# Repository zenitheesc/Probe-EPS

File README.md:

<h1 align="center" style="color:white; background-color:black">Probe-EPS</h1>
<h4 align="center">Eletrical power system for stratospheric probes, using Zenith Stack</h4>

<p align="center">

</p>

<p align="center">
    <a href="#environment-and-tools">Environment and Tools</a> •
    <a href="#z-hub">Z-Hub</a> •
    <a href="#aroca-(battery)-eps">Aroca (Battery) EPS</a> •
    <a href="#london-(power)-eps">London (Power) EPS</a>
</p>

This configuration of the Eletrical power system requires a board that monitors the charger and battery, in addition to performing thermal control.

## Environment and tools

This system was designed using Eagle v.9.4.2

## Z-Hub

<a href="https://github.com/zenitheesc/Probe-EPS/tree/main/Hardware/Aroca_EPS-v.2.0"><h2>Aroca (Battery) EPS</h2></a>

This subsystem is primarily responsible for the active thermal control of the batteries, in addition to supporting battery monitoring and load balancing

<a href="https://github.com/zenitheesc/Probe-EPS/tree/main/Hardware/London_EPS-v.2.0"><h2>London (Power) EPS</h2></a>

Functioning as an extension of the previous subsystem, it performs conversions of battery voltage levels to the levels requested within the hardware, making the necessary distribution, as well as controlling the loading of batteries through solar panels.

---

<p align="center">

</p>
<p align = "center">
<a href="zenith.eesc@gmail.com">zenith.eesc@gmail.com</a>
</p>

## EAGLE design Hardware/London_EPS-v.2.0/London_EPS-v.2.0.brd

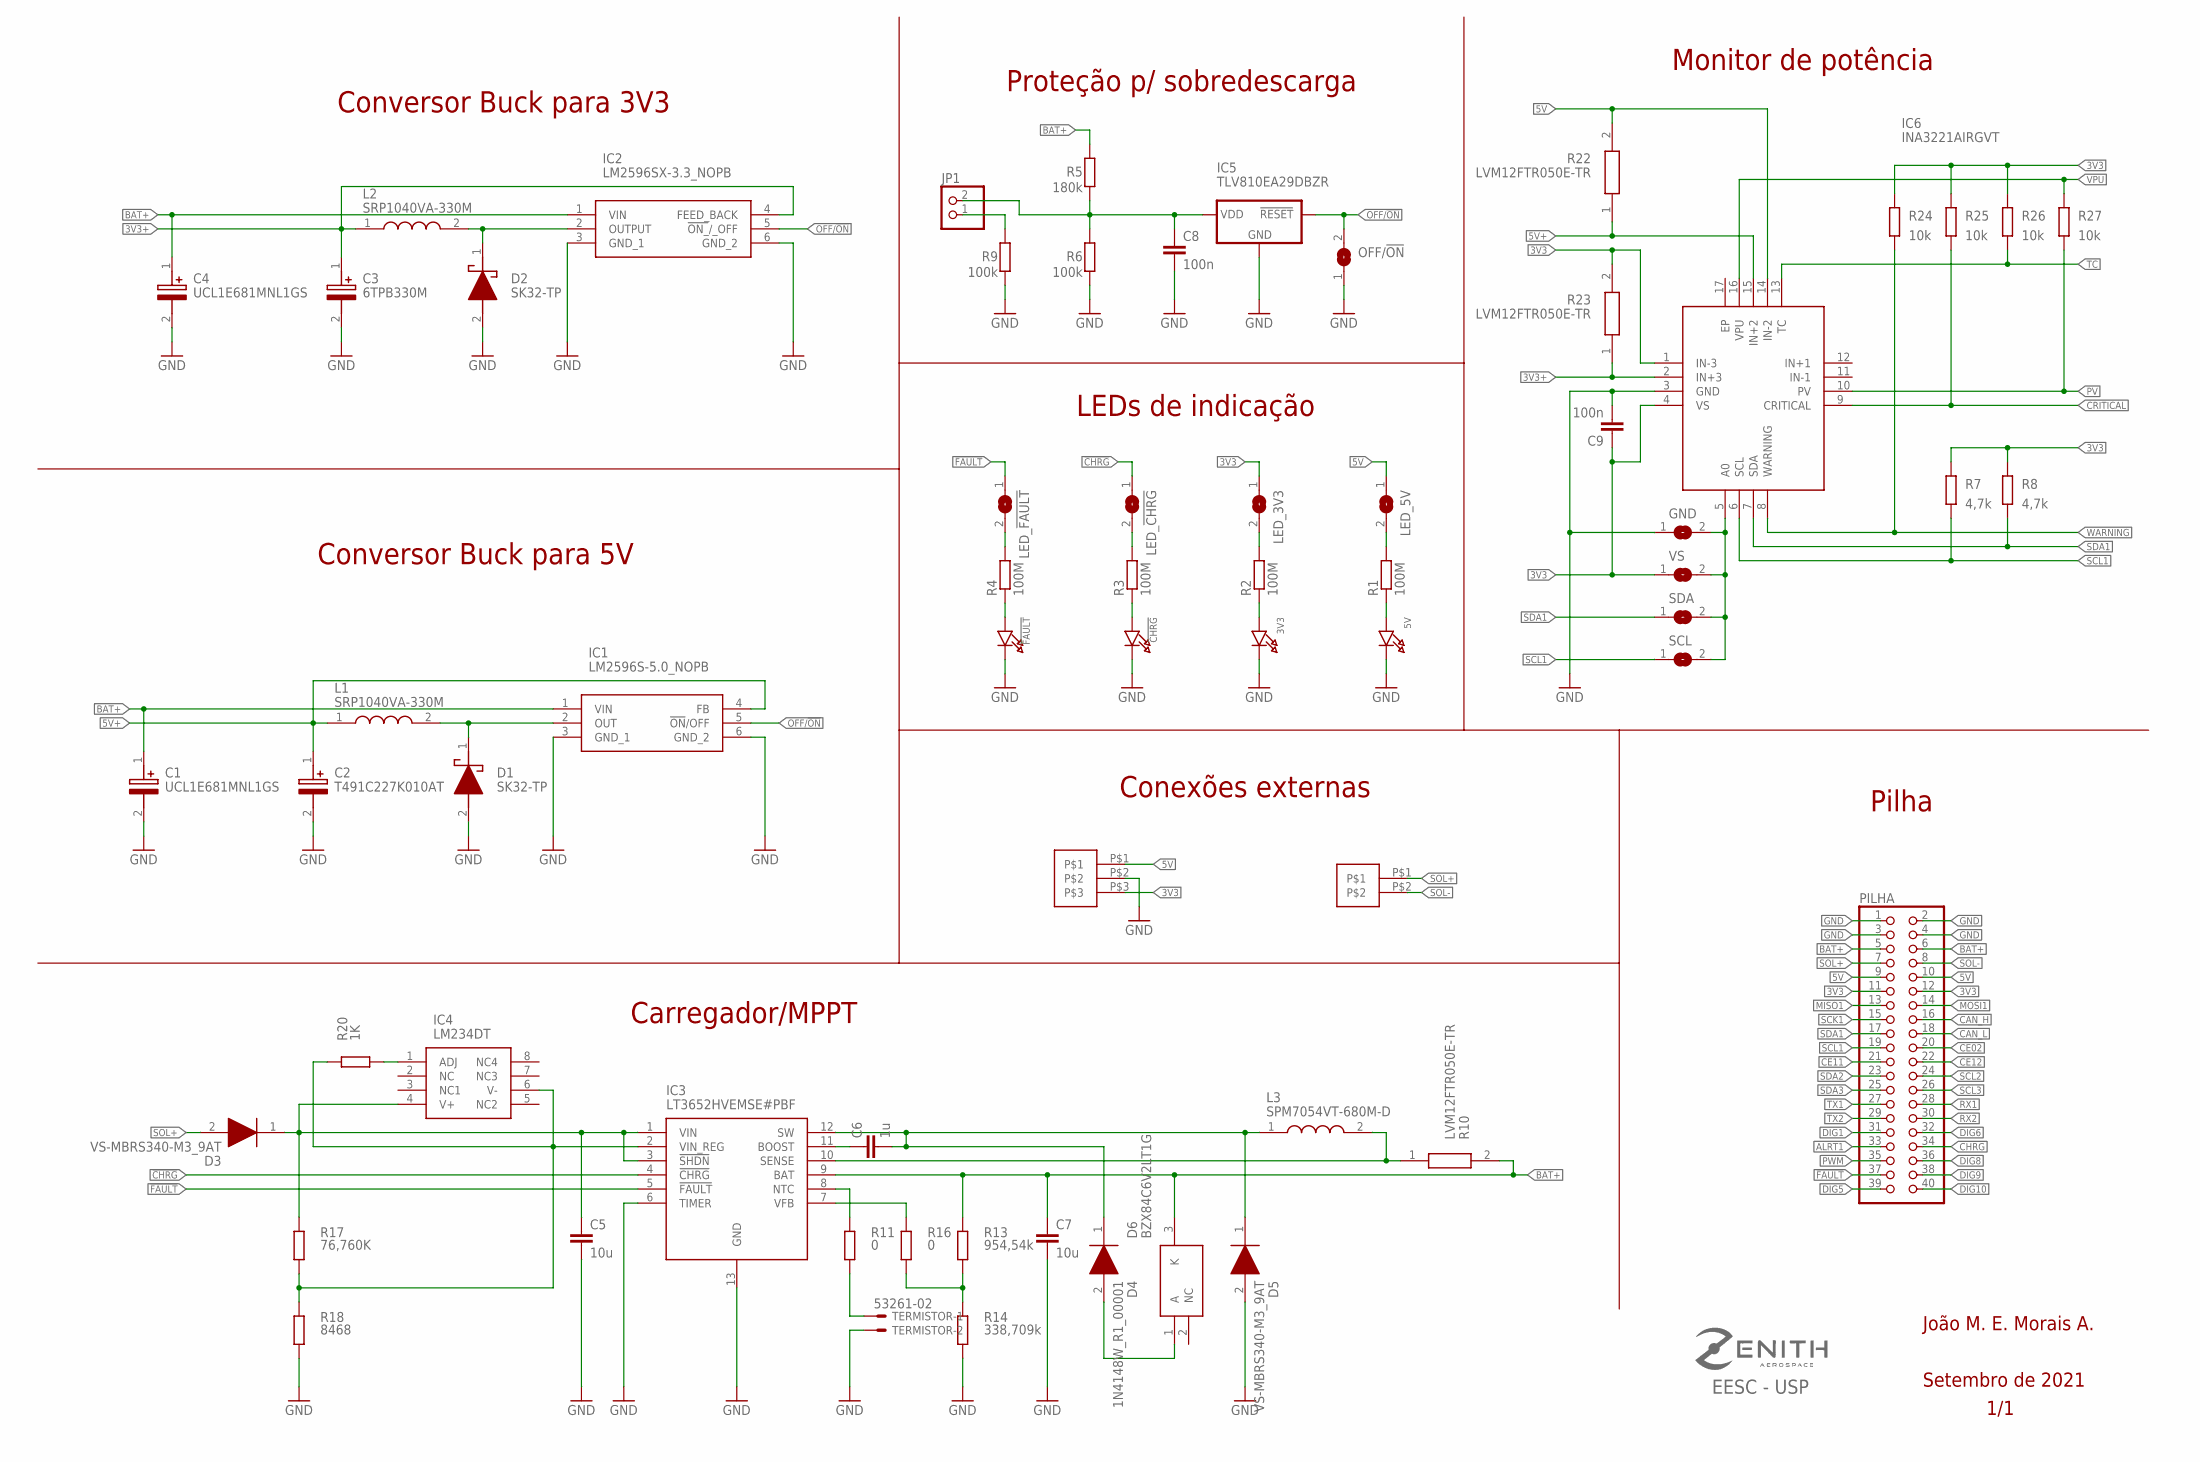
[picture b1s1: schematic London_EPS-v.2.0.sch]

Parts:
3V3, 5V: LED1206; CHIPLED_1206
!CHRG: LED1206; CHIPLED_1206
!FAULT: LED1206; CHIPLED_1206
C1, C4: UCL1E681MNL1GS; CAPAE1030X1400N
C2: T491C227K010AT; CAPPM6032X280N
C3: 6TPB330M; 10TPF150ML
C5, C7: 10u; C0805
C6: 1u; C0805
C8, C9: 100n; C0805
D1, D2: SK32-TP; DIOM7959X262N@1
D3, D5: VS-MBRS340-M3_9AT; DIOM7959X262N
D4: 1N4148W_R1_00001; SOD3816X135N
D6: BZX84C6V2LT1G; SOT96P237X111-3N
GND: SOLDERJUMPERREFLOW_NOPASTE; SOLDERJUMPER_REFLOW_NOPASTE
IC1: LM2596S-5.0_NOPB; KTT0005B
IC2: LM2596SX-3.3_NOPB; KTT0005B
IC3: LT3652HVEMSE#PBF; SOP65P490X110-13N
IC4: LM234DT; SOIC127P600X175-8N
IC5: TLV810EA29DBZR; SOT23
IC6: INA3221AIRGVT; QFN65P400X400X100-17N
JP1: PINHD-1X2/90; 1X02/90
L1, L2: SRP1040VA-330M; INDPM110100X400N
L3: SPM7054VT-680M-D; SPM7054VT
LED_3V3, LED_5V: SOLDERJUMPERREFLOW_NOPASTE; SOLDERJUMPER_REFLOW_NOPASTE
LED_!CHRG: SOLDERJUMPERREFLOW_NOPASTE; SOLDERJUMPER_REFLOW_NOPASTE
LED_!FAULT: SOLDERJUMPERREFLOW_NOPASTE; SOLDERJUMPER_REFLOW_NOPASTE
OFF/!ON: SOLDERJUMPERREFLOW_NOPASTE; SOLDERJUMPER_REFLOW_NOPASTE
PILHA: PINHD-2X20; 2X20
R1, R2, R3, R4: 100M; R0805
R5: 180k; R0805
R6, R9: 100k; R0805
R7, R8: 4,7k; R0805
R10, R22, R23: LVM12FTR050E-TR; RESC3016X70N
R11, R16: 0; R0805
R13: 954,54k; R0805
R14: 338,709k; R0805
R17: 76,760K; R0805
R18: 8468; R0805
R20: 1K; R0805
R24, R25, R26, R27: 10k; R0805
SCL: SOLDERJUMPERREFLOW_NOPASTE; SOLDERJUMPER_REFLOW_NOPASTE
SDA: SOLDERJUMPERREFLOW_NOPASTE; SOLDERJUMPER_REFLOW_NOPASTE
TERMISTOR: 53261-02
U$1: S02B-XASS-1
U$2: S03B-XASS-1
VS: SOLDERJUMPERREFLOW_NOPASTE; SOLDERJUMPER_REFLOW_NOPASTE

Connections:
3V3: C9.1, IC6.1 (IN-3), IC6.4 (VS), LED_3V3.1, PILHA.11, PILHA.12, R7.2, R8.2, R23.2, R24.2, R25.2, R26.2, U$2.P$3, VS.1
3V3+: C3.1 (+), IC2.4 (FEED_BACK), IC6.2 (IN+3), L2.1, R23.1
5V: IC6.14 (IN-2), LED_5V.1, PILHA.9, PILHA.10, R22.2, U$2.P$1
5V+: C2.1 (+), IC1.4 (FB), IC6.15 (IN+2), L1.1, R22.1
!CHRG: IC3.4 (!CHRG), LED_!CHRG.1, PILHA.34
!FAULT: IC3.5 (!FAULT), LED_!FAULT.1, PILHA.37
ALRT1: PILHA.33
BAT+: C1.1 (+), C4.1 (+), C7.1, D6.3 (K), IC1.1 (VIN), IC2.1 (VIN), IC3.9 (BAT), PILHA.5, PILHA.6, R5.1, R10.2, R13.1
CAN_H: PILHA.16
CAN_L: PILHA.18
CE02: PILHA.20
CE11: PILHA.21
CE12: PILHA.22
CRITICAL: IC6.9 (CRITICAL), R25.1
DIG1: PILHA.31
DIG5: PILHA.39
DIG6: PILHA.32
DIG8: PILHA.36
DIG9: PILHA.38
DIG10: PILHA.40
GND: 3V3.C, 5V.C, !CHRG.C, !FAULT.C, C1.2 (-), C2.2 (-), C3.2 (-), C4.2 (-), C5.2, C7.2, C8.2, C9.2, D1.2 (A), D2.2 (A), D5.2 (A), GND.1, IC1.3 (GND_1), IC1.6 (GND_2), IC2.3 (GND_1), IC2.6 (GND_2), IC3.6 (TIMER), IC3.13 (GND), IC5.2 (GND), IC6.3 (GND), OFF/!ON.1, PILHA.1, PILHA.2, PILHA.3, PILHA.4, R6.2, R9.2, R14.2, R18.2, TERMISTOR.2, U$2.P$2
MISO1: PILHA.13
MOSI1: PILHA.14
unnamed: 5V.A, R1.1
unnamed: LED_5V.2, R1.2
unnamed: 3V3.A, R2.1
unnamed: LED_3V3.2, R2.2
unnamed: !CHRG.A, R3.1
unnamed: D2.1 (K), IC2.2 (OUTPUT), L2.2
unnamed: LED_!CHRG.2, R3.2
unnamed: D1.1 (K), IC1.2 (OUT), L1.2
unnamed: !FAULT.A, R4.1
unnamed: LED_!FAULT.2, R4.2
unnamed: C8.1, IC5.3 (VDD), JP1.2, R5.2, R6.1
unnamed: GND.2, IC6.5 (A0), SCL.2, SDA.2, VS.2
unnamed: JP1.1, R9.1
unnamed: IC3.10 (SENSE), L3.2, R10.1
unnamed: IC3.8 (NTC), R11.1
unnamed: R11.2, TERMISTOR.1
unnamed: C6.2, D4.1 (K), D5.1 (K), IC3.12 (SW), L3.1
unnamed: IC3.7 (VFB), R16.1
unnamed: R13.2, R14.1, R16.2
unnamed: C6.1, IC3.11 (BOOST)
unnamed: C5.1, D3.1 (K), IC3.1 (VIN), IC3.3 (!SHDN), IC4.4 (V+), R17.1
unnamed: IC3.2 (VIN_REG), IC4.6 (V-), R17.2, R18.1, R20.1
unnamed: IC4.1 (ADJ), R20.2
unnamed: D4.2 (A), D6.1 (A)
OFF/!ON: IC1.5 (!ON!/OFF), IC2.5 (!ON_!/_OFF), IC5.1 (!RESET), OFF/!ON.2
PV: IC6.10 (PV), R27.1
PWM: PILHA.35
RX1: PILHA.28
RX2: PILHA.30
SCK1: PILHA.15
SCL1: IC6.6 (SCL), PILHA.19, R7.1, SCL.1
SCL2: PILHA.24
SCL3: PILHA.26
SDA1: IC6.7 (SDA), PILHA.17, R8.1, SDA.1
SDA2: PILHA.23
SDA3: PILHA.25
SOL+: D3.2 (A), PILHA.7, U$1.P$1
SOL-: PILHA.8, U$1.P$2
TC: IC6.13 (TC), R26.1
TX1: PILHA.27
TX2: PILHA.29
VPU: IC6.16 (VPU), R27.2
WARNING: IC6.8 (WARNING), R24.1

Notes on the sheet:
C:/Users/marcu/Desktop/Ensino Superior/Graduação - Eng Elétrica/Zenith/zenith-v2.bmp
EESC - USP
Setembro de 2021
1/1
João M. E. Morais A.
Pilha
Monitor de potência
Carregador/MPPT
Conversor Buck para 5V
Conversor Buck para 3V3
Proteção p/ sobredescarga
LEDs de indicação
Conexões externas

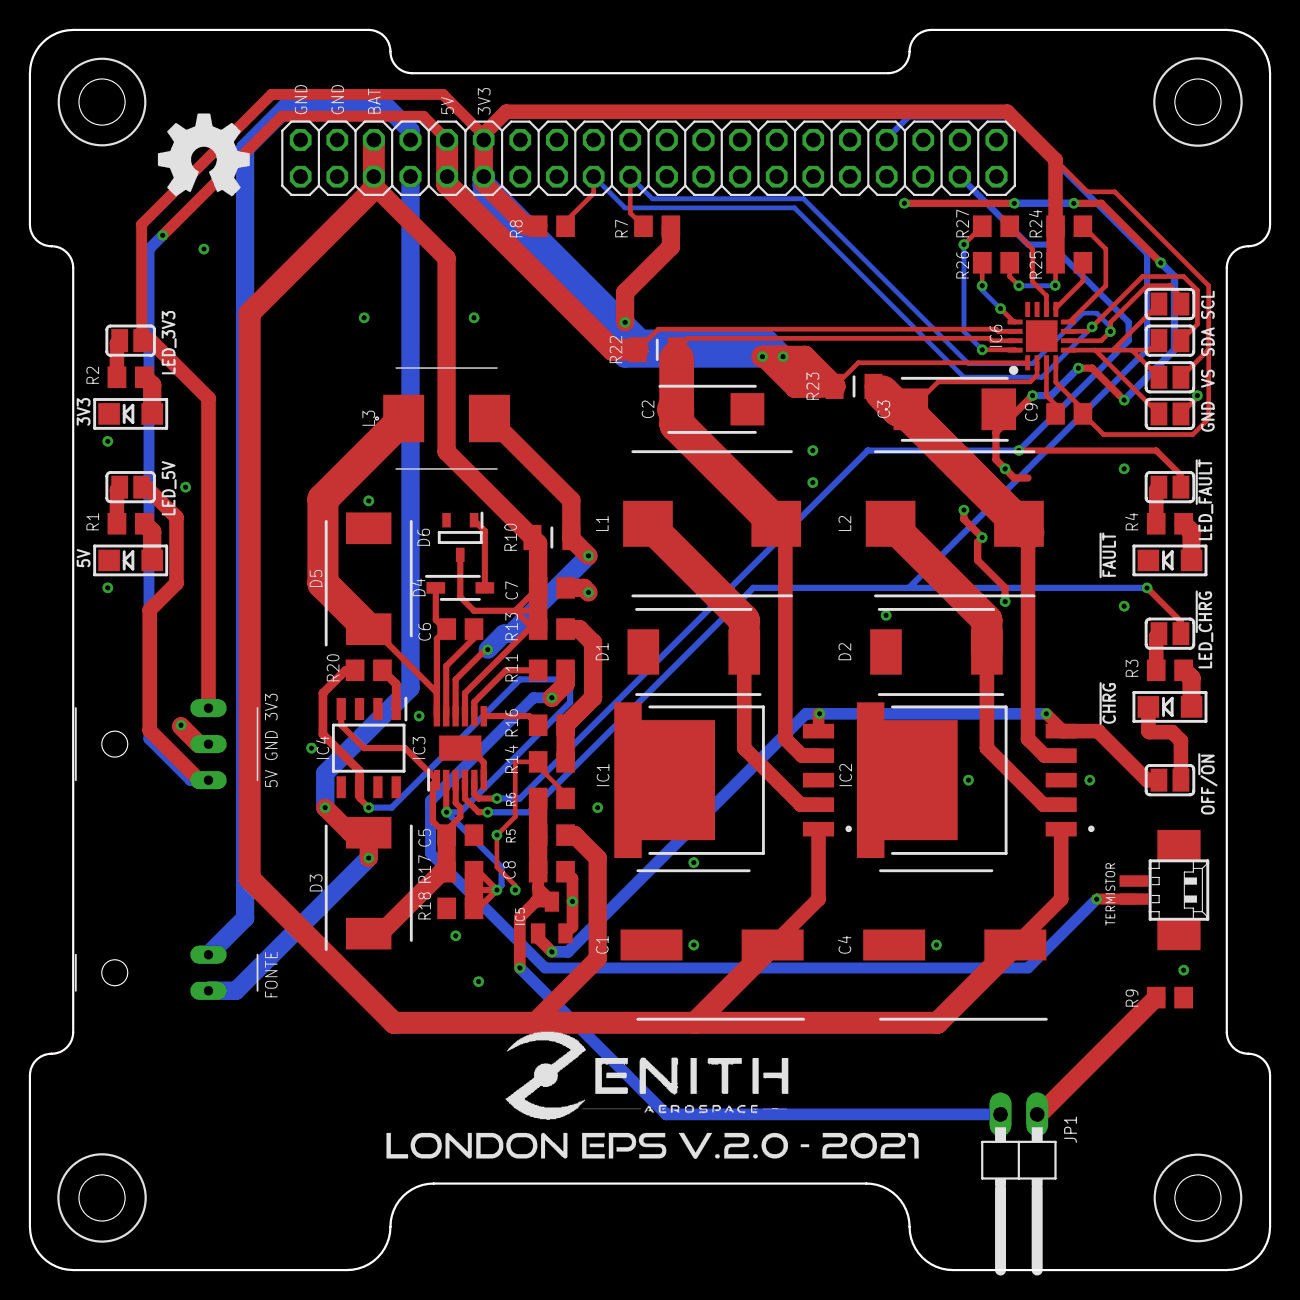
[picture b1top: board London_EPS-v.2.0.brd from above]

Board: 2 copper layers, 86.0 x 86.0 mm, 65 parts (0 on the bottom side), 42 nets.

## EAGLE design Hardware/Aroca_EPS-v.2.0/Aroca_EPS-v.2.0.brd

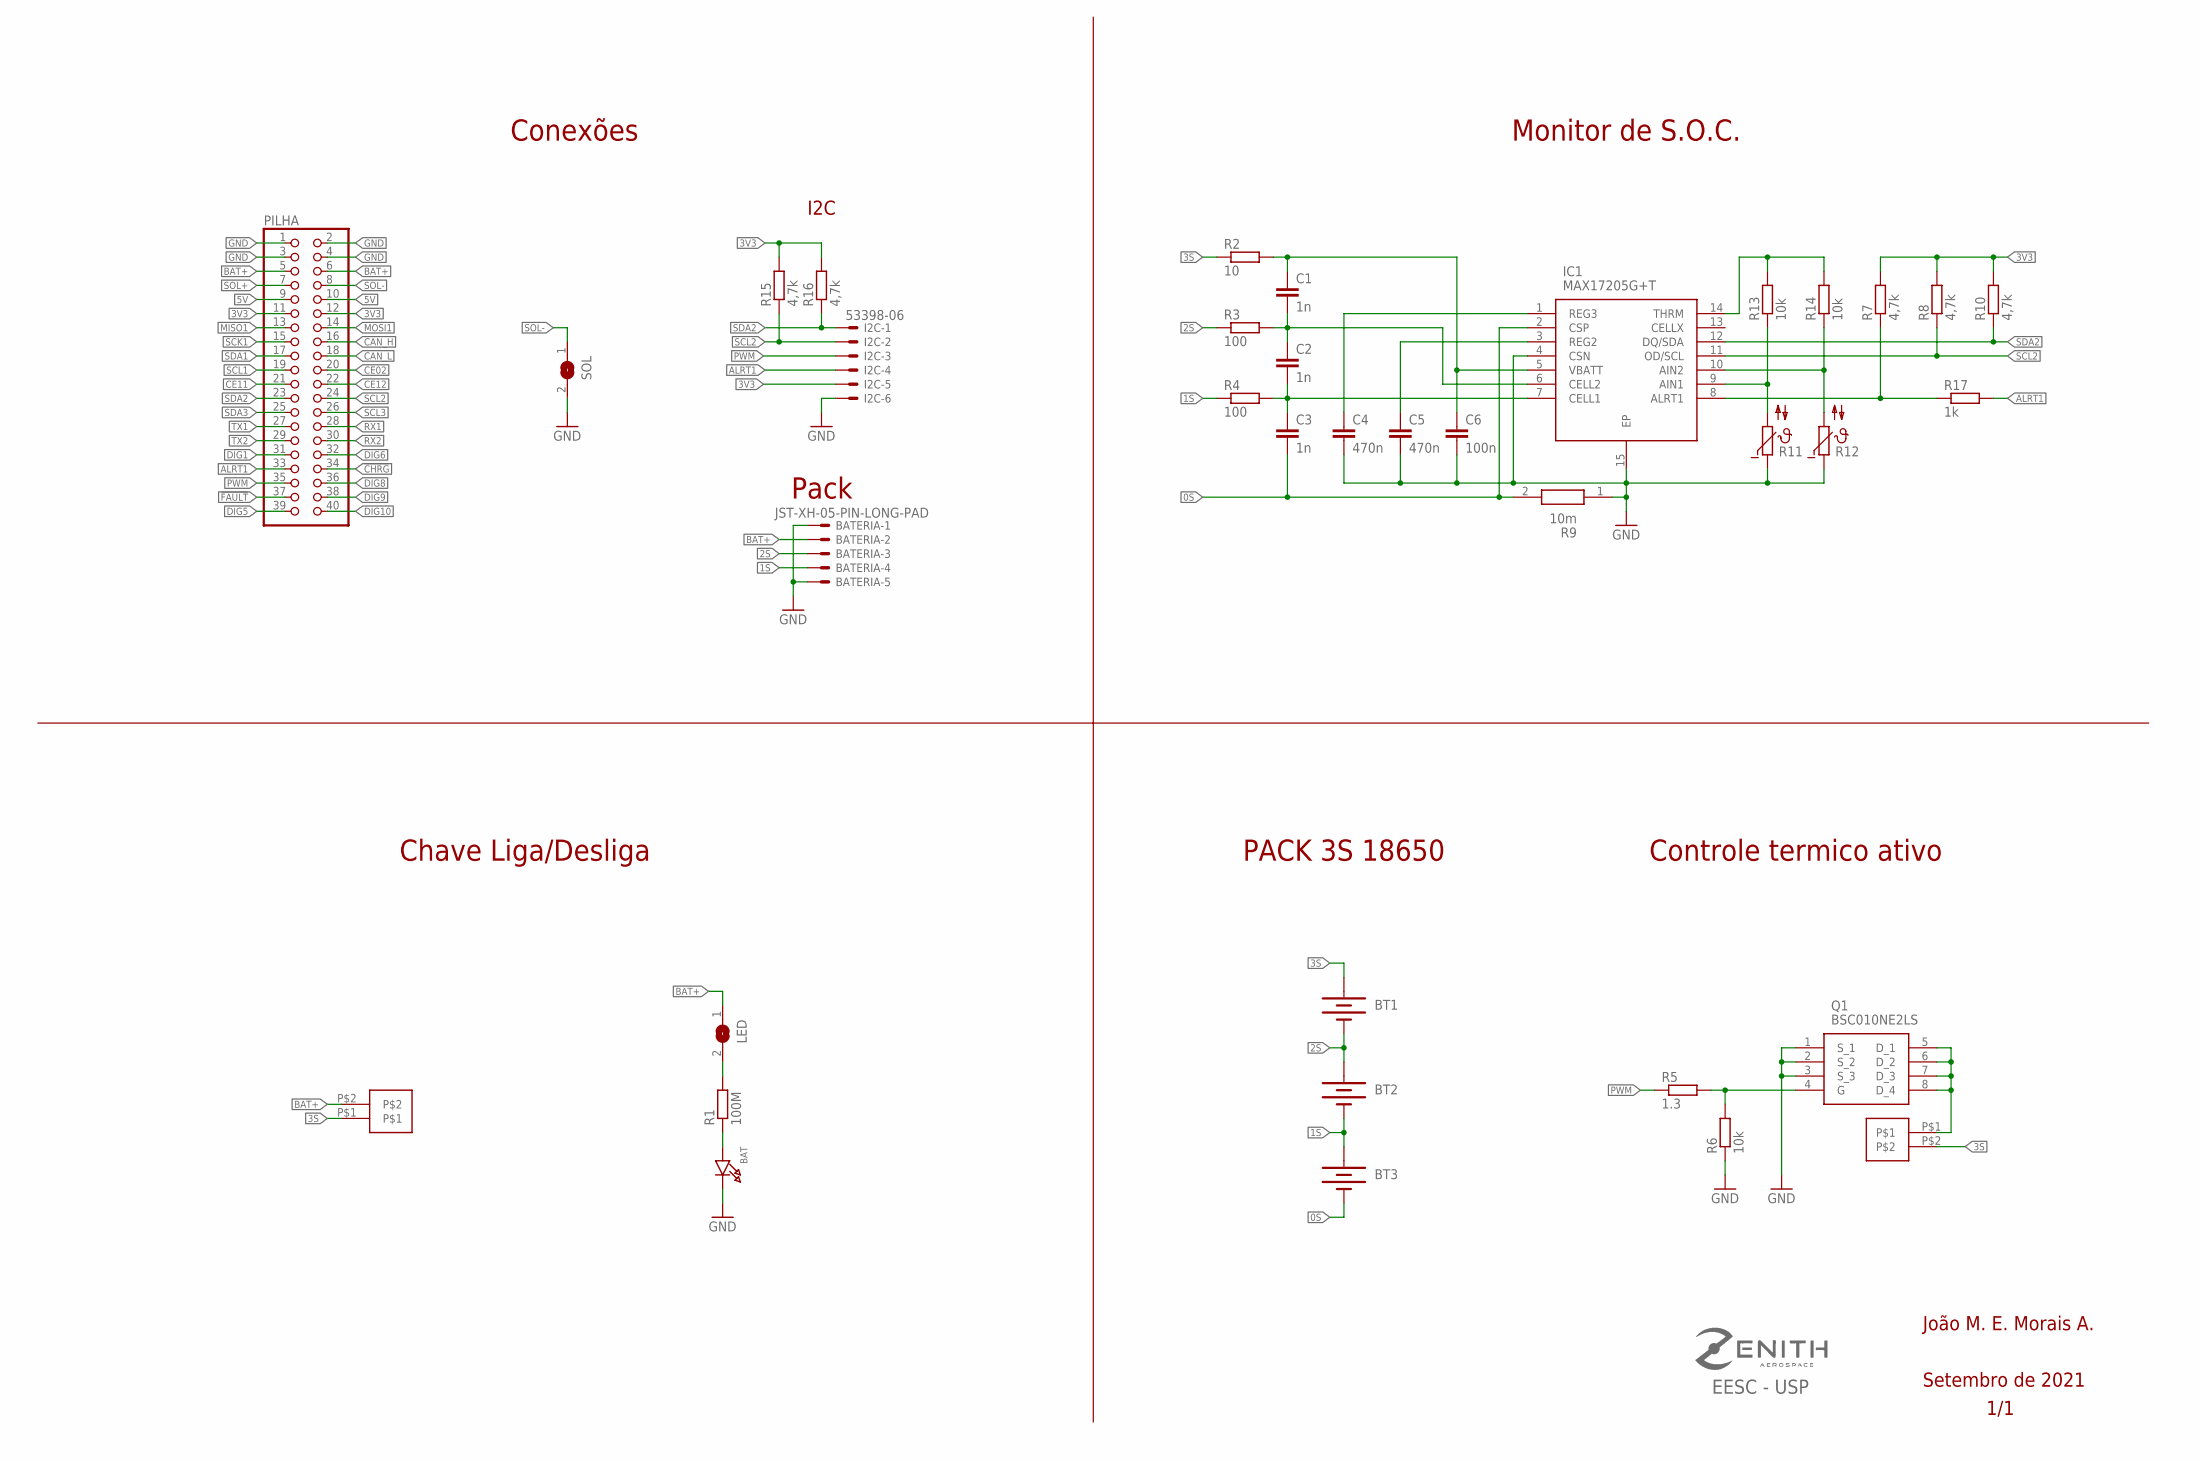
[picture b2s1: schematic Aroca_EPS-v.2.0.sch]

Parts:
BAT: LED1206; CHIPLED_1206
BATERIA: JST-XH-05-PIN-LONG-PAD; JST-XH-05-PACKAGE-LONG-PAD
BT1, BT2, BT3: BATTERY-18650; BATTERY_18650-HOLDER
C1, C2, C3: 1n; C0805
C4, C5: 470n; C0805
C6: 100n; C0805
I2C: 53398-06
IC1: MAX17205G+T; SON40P300X300X80-15N
LED: SOLDERJUMPERREFLOW_NOPASTE; SOLDERJUMPER_REFLOW_NOPASTE
PILHA: PINHD-2X20; 2X20
Q1: BSC010NE2LS; PG-TDSON-8
R1: 100M; R0805
R2: 10; 0204/7
R3, R4: 100; 0204/7
R5: 1.3; R0805
R6, R13, R14: 10k; R0805
R7, R8, R10, R15, R16: 4,7k; R0805
R9: 10m; GMR320HJBFA10L0
R11, R12: NTC640; P640
R17: 1k; R0805
SOL: SOLDERJUMPERREFLOW_NOPASTE; SOLDERJUMPER_REFLOW_NOPASTE
U$1: S02B-XASS-1
U$2: B02B-XASK-1

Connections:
0S: BT3.GND@1 (-), C3.2, IC1.2 (CSP), R9.2
1S: BATERIA.4, BT2.GND@1 (-), BT3.PWR@1 (+), R4.1
2S: BATERIA.3, BT1.GND@1 (-), BT2.PWR@1 (+), R3.1
3S: BT1.PWR@1 (+), R2.1, U$1.P$1, U$2.P$2
3V3: I2C.5, PILHA.11, PILHA.12, R7.2, R8.2, R10.2, R15.2, R16.2
5V: PILHA.9, PILHA.10
!CHRG: PILHA.34
!FAULT: PILHA.37
ALRT: IC1.8 (ALRT1), R7.1, R17.1
ALRT1: I2C.4, PILHA.33, R17.2
BAT+: BATERIA.2, LED.1, PILHA.5, PILHA.6, U$1.P$2
CAN_H: PILHA.16
CAN_L: PILHA.18
CE02: PILHA.20
CE11: PILHA.21
CE12: PILHA.22
DIG1: PILHA.31
DIG5: PILHA.39
DIG6: PILHA.32
DIG8: PILHA.36
DIG9: PILHA.38
DIG10: PILHA.40
GND: BAT.C, BATERIA.1, BATERIA.5, C4.2, C5.2, C6.2, I2C.6, IC1.4 (CSN), IC1.15 (EP), PILHA.1, PILHA.2, PILHA.3, PILHA.4, Q1.1 (S_1), Q1.2 (S_2), Q1.3 (S_3), R6.1, R9.1, R11.1, R12.1, SOL.2
MISO1: PILHA.13
MOSI1: PILHA.14
unnamed: BAT.A, R1.1
unnamed: LED.2, R1.2
unnamed: Q1.4 (G), R5.2, R6.2
unnamed: C4.1, IC1.1 (REG3)
unnamed: C5.1, IC1.3 (REG2)
unnamed: C1.1, C6.1, IC1.5 (VBATT), R2.2
unnamed: C2.2, C3.1, IC1.7 (CELL1), R4.2
unnamed: C1.2, C2.1, IC1.6 (CELL2), R3.2
unnamed: IC1.14 (THRM), R13.2, R14.2
unnamed: IC1.9 (AIN1), R11.2, R13.1
unnamed: IC1.10 (AIN2), R12.2, R14.1
PWM: I2C.3, PILHA.35, R5.1
RL: Q1.5 (D_1), Q1.6 (D_2), Q1.7 (D_3), Q1.8 (D_4), U$2.P$1
RX1: PILHA.28
RX2: PILHA.30
SCK1: PILHA.15
SCL1: PILHA.19
SCL2: I2C.2, IC1.11 (OD/SCL), PILHA.24, R8.1, R15.1
SCL3: PILHA.26
SDA1: PILHA.17
SDA2: I2C.1, IC1.12 (DQ/SDA), PILHA.23, R10.1, R16.1
SDA3: PILHA.25
SOL+: PILHA.7
SOL-: PILHA.8, SOL.1
TX1: PILHA.27
TX2: PILHA.29

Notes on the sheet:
C:/Users/marcu/Desktop/Ensino Superior/Graduação - Eng Elétrica/Zenith/zenith-v2.bmp
EESC - USP
Setembro de 2021
1/1
João M. E. Morais A.
Conexões
PACK 3S 18650
Controle termico ativo
Monitor de S.O.C.
Chave Liga/Desliga
I2C
Pack

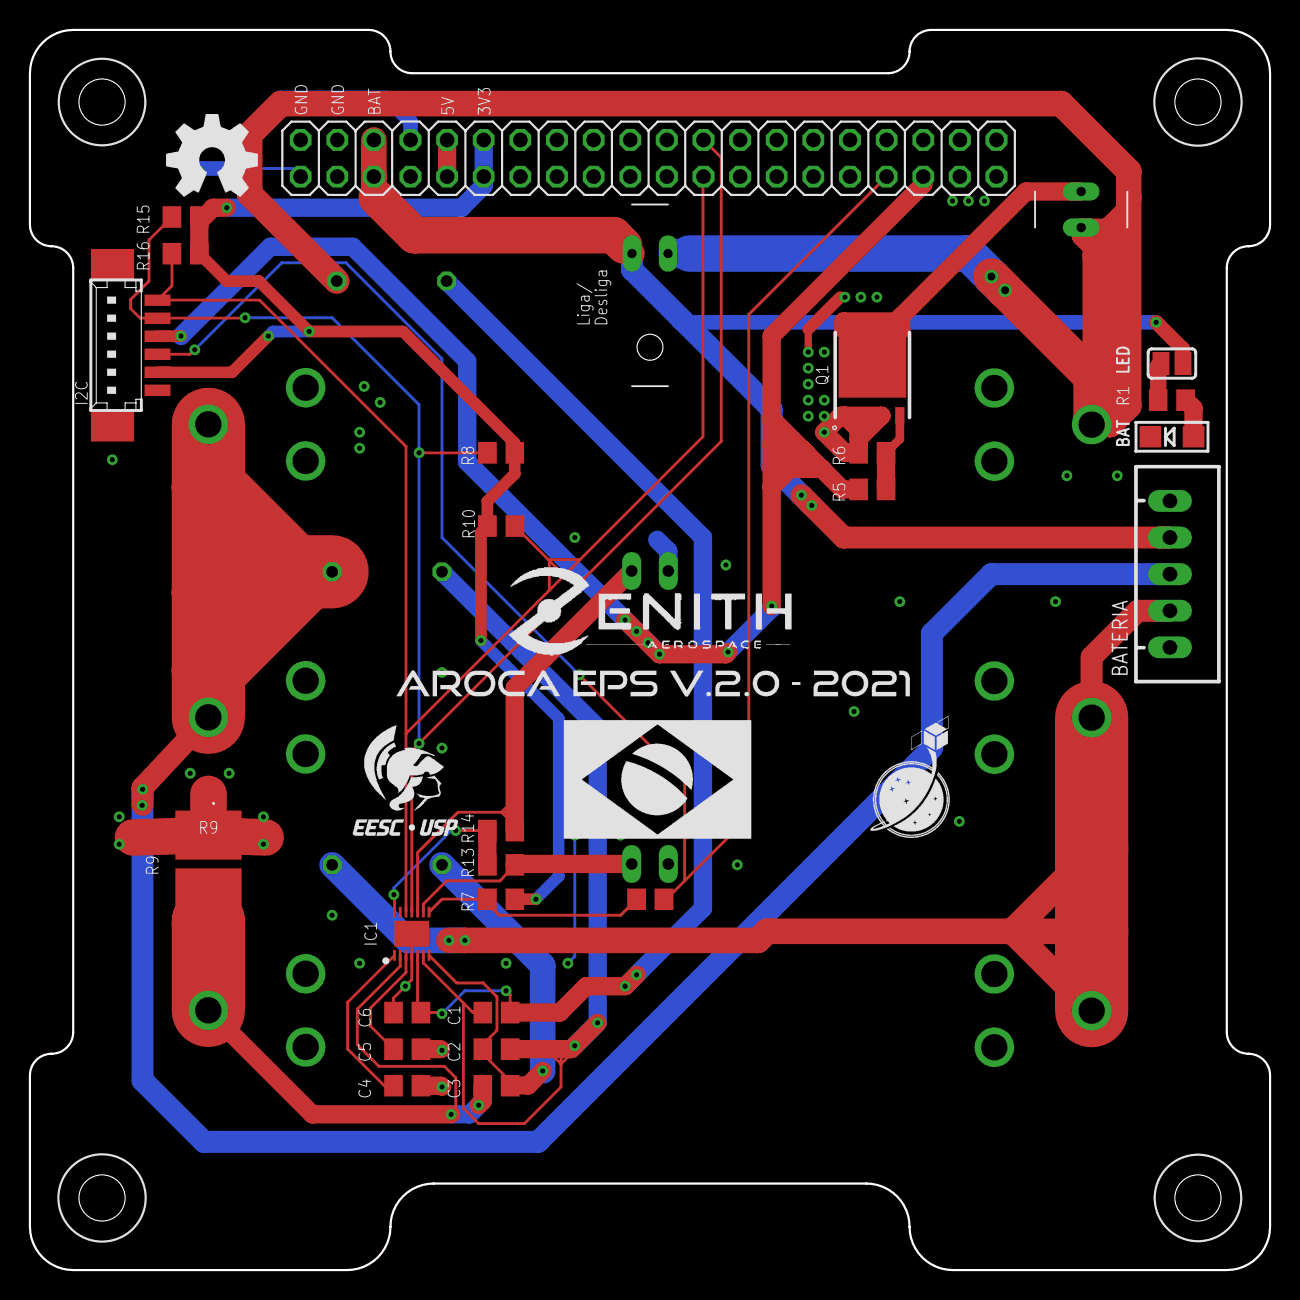
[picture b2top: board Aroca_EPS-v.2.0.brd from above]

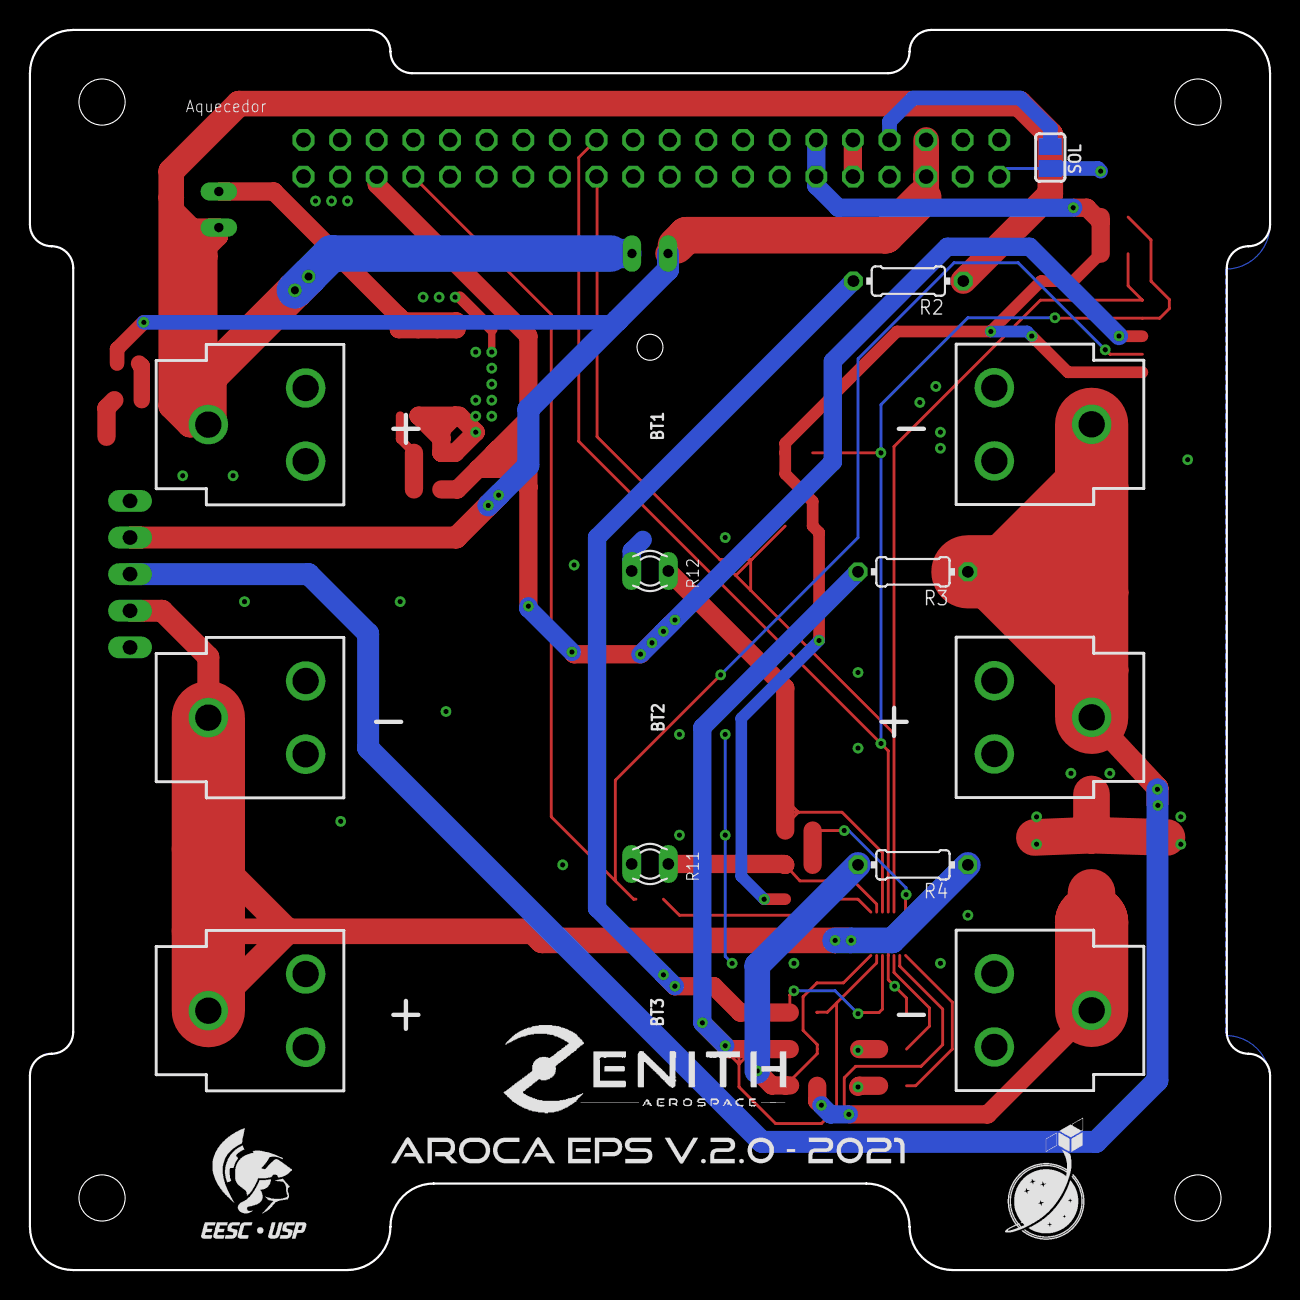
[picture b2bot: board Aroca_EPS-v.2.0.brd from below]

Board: 2 copper layers, 86.0 x 86.0 mm, 36 parts (9 on the bottom side), 26 nets.

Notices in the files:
parts and their libraries:
SparkFun-Batteries: Licensing: Creative Commons ShareAlike 4.0 International - https://creativecommons.org/licenses/by-sa/4.0
